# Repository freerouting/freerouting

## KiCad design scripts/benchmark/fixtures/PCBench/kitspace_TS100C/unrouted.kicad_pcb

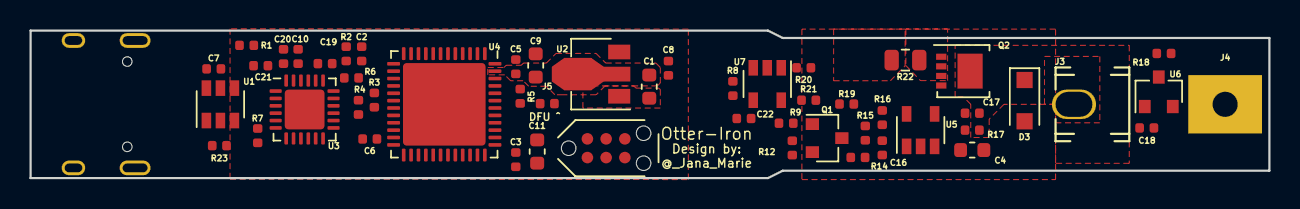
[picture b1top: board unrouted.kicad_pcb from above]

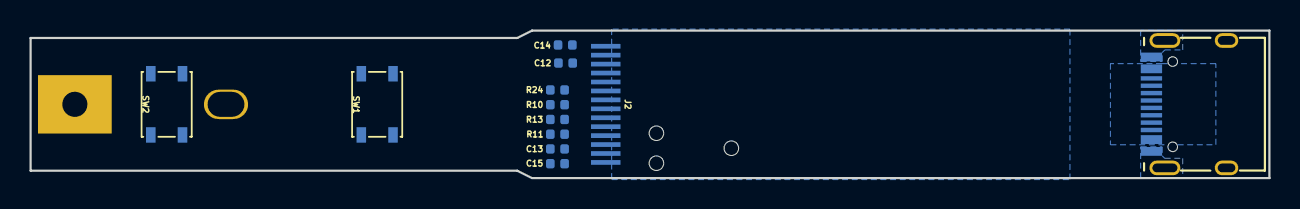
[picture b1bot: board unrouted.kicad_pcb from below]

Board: 2 copper layers, 84.0 x 10.0 mm, 64 parts (12 on the bottom side), 42 nets, no tracks yet.

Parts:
C1, C4, C9, C11: 1μF 25V; C_0603_1608Metric
C2, C3, C5, C6, C7, C8, C10, C18, C21, C22: 0.1μF; C_0402_1005Metric
C12, C13, C14, C15, C19, C20: 1μF 25V; C_0402_1005Metric
C16: 18p; C_0402_1005Metric
C17: DNP; C_0402_1005Metric
D3: B140-E3; D_SOD-123F
J1: USB_C_Receptacle_USB2.0; USB-C 16Pin
J2: OLED_64x32; 0.69OLED
J3: A; Keystone_3621
J4: B; 3622TR
J5: DNP; R_0402_1005Metric
P1: TC2030-CTX; TC2030-NL_SMALL
Q1: SS8050; SOT-23
Q2: DMP3017SFG; Diodes_PowerDI3333-8
R1, R11: 560k; R_0402_1005Metric
R2, R17: 100k; R_0402_1005Metric
R3, R4, R5, R6, R7, R8, R9, R10, R12, R13, R14, R16, R18, R23, R24: 2k37; R_0402_1005Metric
R15: 750k; R_0402_1005Metric
R19: 20; R_0402_1005Metric
R20, R21: 33; R_0402_1005Metric
R22: 10m; R_0805_2012Metric
SW1: key1; SW_SPST_PTS810
SW2: key2; SW_SPST_PTS810
U1: USBLC6-4SC6; SOT-23-6
U2: AP2204R-3.3; SOT-89-3
U3: STUSB4500QTR; QFN-24-1EP_4x4mm_P0.5mm_EP2.7x2.7mm
U4: STM32F072CBUx; QFN-48-1EP_7x7mm_P0.5mm_EP5.6x5.6mm
U5: OPA340NA; SOT-23-5
U6: MCP9700AT-ETT; SOT-23
U7: SI8540; SOT-23-5

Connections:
/OUT: C17.2, D3.1, J3.1, Q2.5, R17.1
CC1: J1.A5, U1.4, U3.1, U3.2
CC2: J1.B5, U1.3, U3.4, U3.5
IIN: C22.1, R8.1, U4.10, U7.4
INT_N: R6.1, U3.19, U4.25
unnamed: C12.1, J2.3
unnamed: C12.2, J2.4
unnamed: C13.1, J2.13
unnamed: C14.1, J2.2
unnamed: C15.1, J2.14
unnamed: C16.1, R15.1, R16.2, U5.4
unnamed: C16.2, R14.1, R15.2, U5.1
unnamed: C19.2, U3.21
unnamed: C20.1, U3.23
unnamed: J2.9, R24.1
unnamed: J2.12, R11.1
unnamed: J5.1, R5.2, U4.44
unnamed: Q1.1, R9.2
unnamed: Q1.3, R12.2, R19.1
unnamed: Q2.1, Q2.2, Q2.3, R21.2, R22.2
unnamed: Q2.4, R19.2
unnamed: R7.2, U3.6
unnamed: R17.2, U5.3
unnamed: R18.2, U6.2
unnamed: R20.2, U7.1
unnamed: R21.1, U7.5
unnamed: R23.1, U3.18
unnamed: SW1.2, U4.13
unnamed: SW2.2, U4.14
OLED_SCL: J2.10, R10.1, U4.42
OLED_SDA: J2.11, R13.1, U4.43
PWM: R9.1, U4.29
SCL: R3.1, U3.7, U4.21
SDA: R4.1, U3.8, U4.22
SWCLK: P1.4, U4.37
SWDIO: P1.2, U4.34
TREF: R18.1, U4.15
TTIP: R14.2, U4.11
UIN: C2.1, R1.2, R2.1, U4.12
USB_N: J1.A7, J1.B7, U1.1, U4.32
USB_P: J1.A6, J1.B6, U1.6, U4.33
nRST: P1.3, U4.7

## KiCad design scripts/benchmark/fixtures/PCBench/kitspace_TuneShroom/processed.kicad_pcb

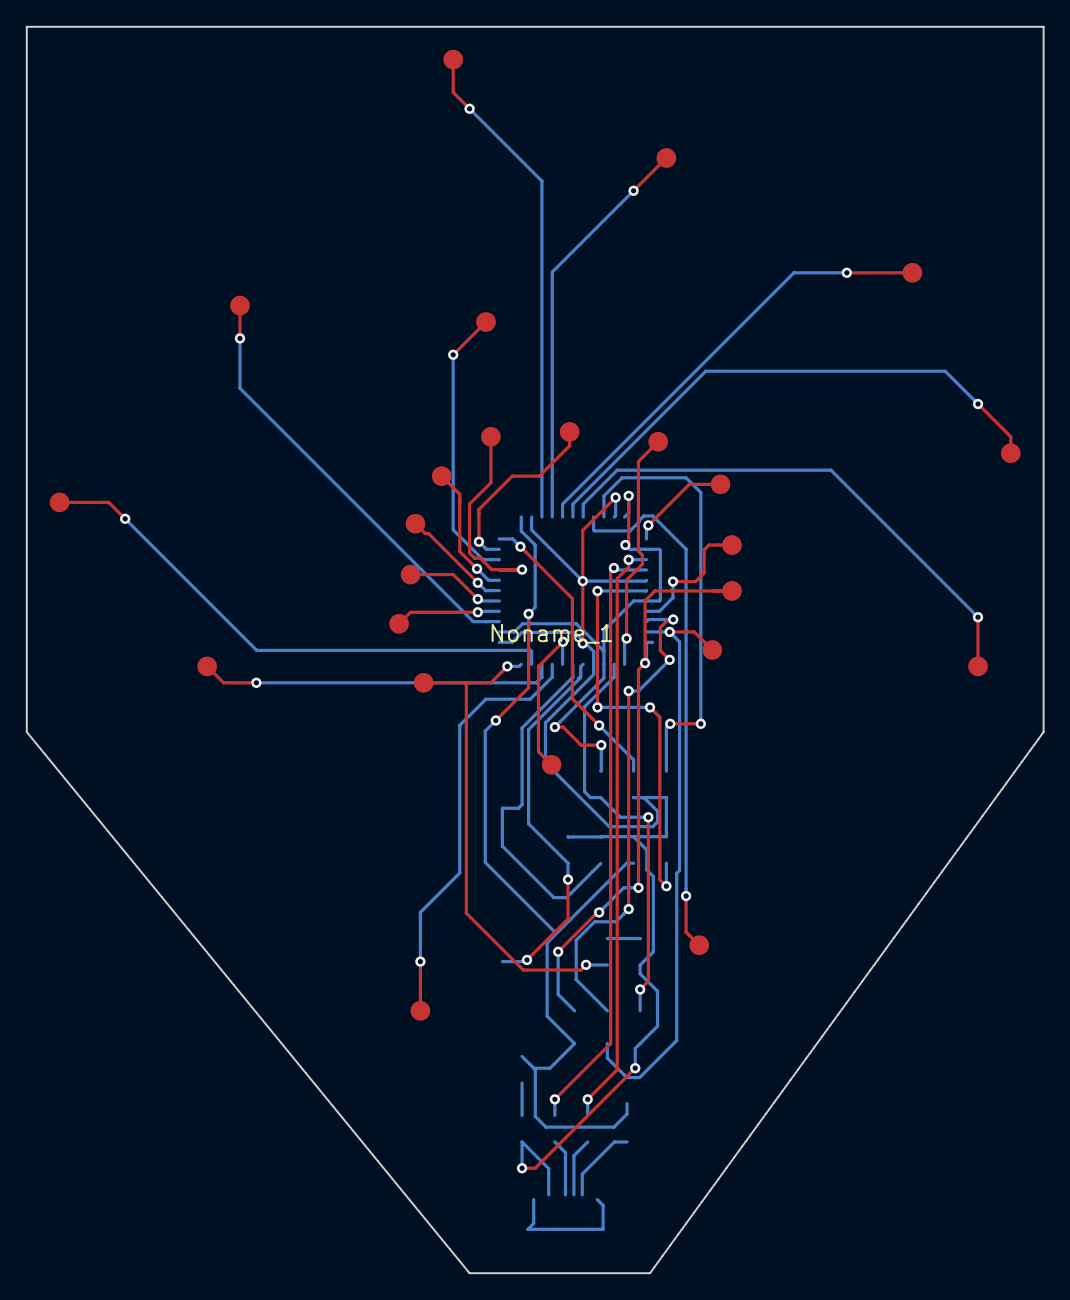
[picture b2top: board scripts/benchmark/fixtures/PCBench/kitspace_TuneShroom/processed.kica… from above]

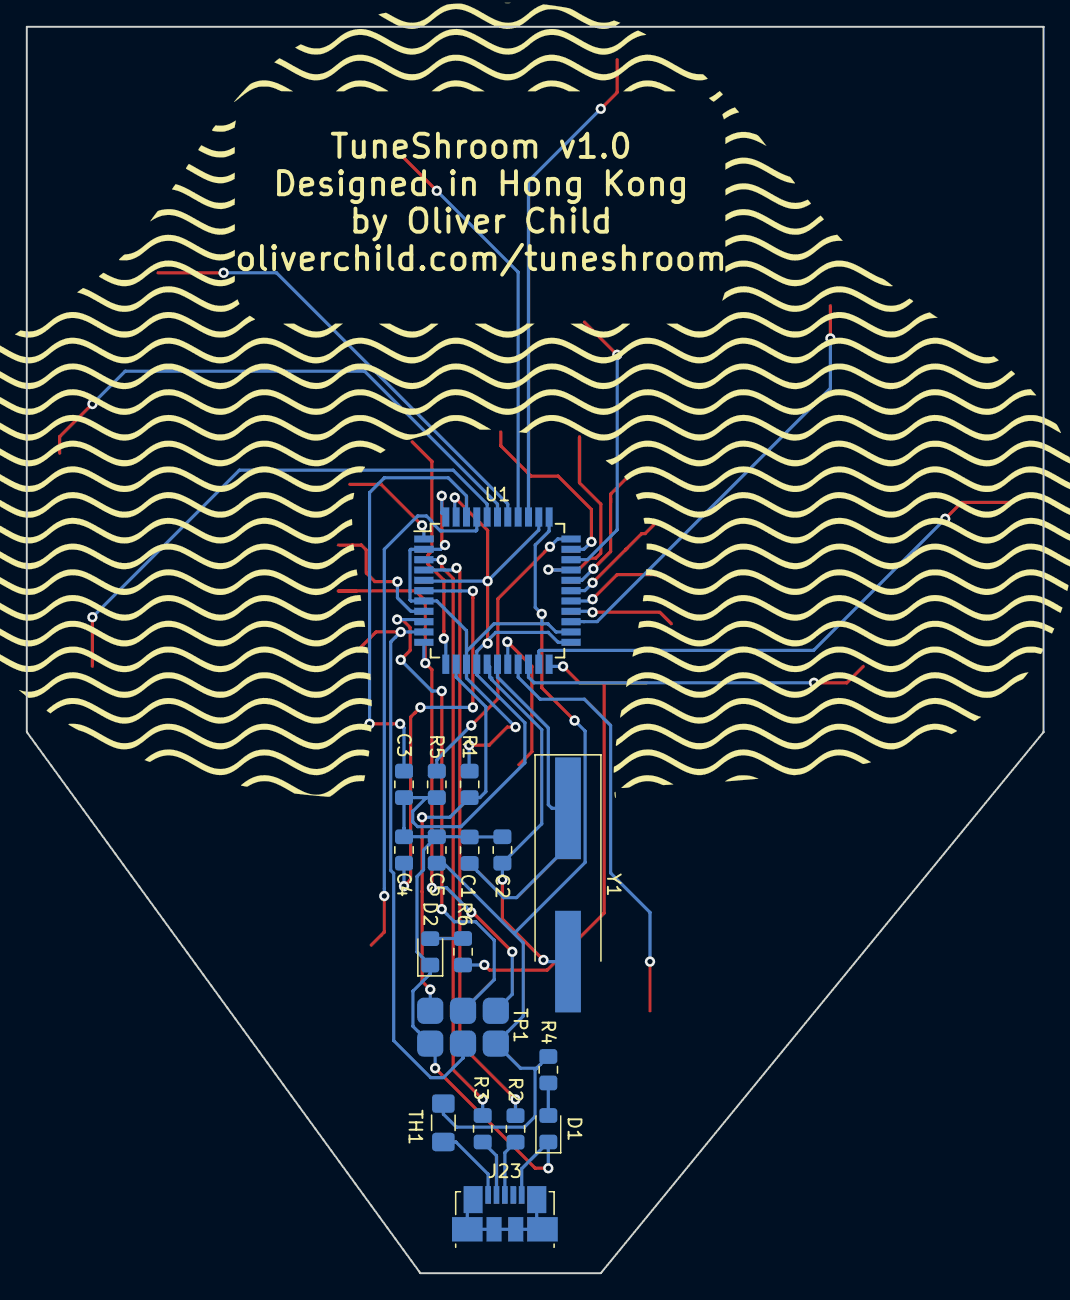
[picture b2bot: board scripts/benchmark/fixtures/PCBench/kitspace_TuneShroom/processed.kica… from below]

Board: 2 copper layers, 78.7 x 96.5 mm, 43 parts (18 on the bottom side), 40 nets.

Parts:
C1, C2: 22pF; C_0805_2012Metric_Pad1.15x1.40mm_HandSolder
C3, C5: 0.1uF; C_0805_2012Metric_Pad1.15x1.40mm_HandSolder
C4: 1uF; C_0805_2012Metric_Pad1.15x1.40mm_HandSolder
D1, D2: LED; LED_0805_2012Metric_Pad1.15x1.40mm_HandSolder
J1, J2, J3, J4, J5, J6, J7, J8, J9, J10, J11, J12, J13, J14, J15, J16, J17, J18, J19, J20, J21, J22, J24, J25: Conn_01x01; contact
J23: USB_B_Micro; USB_Micro-B_Molex_47346-0001
Noname_1: pattern
R1, R5: 10K; R_0805_2012Metric_Pad1.15x1.40mm_HandSolder
R2, R3: 22; R_0805_2012Metric_Pad1.15x1.40mm_HandSolder
R4, R6: 330; R_0805_2012Metric_Pad1.15x1.40mm_HandSolder
TH1: Thermistor; Fuse_1206_3216Metric_Pad1.42x1.75mm_HandSolder
TP1: ICSP
U1: ATmega32U4-AU; TQFP-44_10x10mm_P0.8mm
Y1: 16MHz; Crystal_SMD_HC49-SD_HandSoldering

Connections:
+5V: C5.1, R1.1, R4.1, TH1.1, TP1.2, U1.2, U1.7, U1.14, U1.24, U1.34, U1.44
A0: J1.1, U1.36
A1: J3.1, U1.37
A2: J5.1, U1.38
A3: J7.1, U1.39
A4: J9.1, U1.40
A5: J11.1, U1.41
D0: J13.1, U1.20
D1: J15.1, U1.21
D2: J17.1, U1.19
D3: J19.1, U1.18
D4: J21.1, U1.25
D5: J2.1, U1.31
D6: J4.1, U1.27
D7: J6.1, U1.1
D8: J8.1, U1.28
D9: J10.1, U1.29
D10: J12.1, U1.30
D11: J14.1, U1.12
D12: J16.1, U1.26
D13: J18.1, U1.32
D17: J20.1, U1.8
D+: R2.1, U1.4
D-: R3.1, U1.3
GND: C1.2, C2.2, C3.2, C4.2, C5.2, D1.1, D2.1, J23.5, R5.2, TP1.6, U1.5, U1.15, U1.23, U1.35, U1.43
MISO: J22.1, TP1.1, U1.11
MOSI: J24.1, TP1.4, U1.10
unnamed: C1.1, U1.17, Y1.1
unnamed: C2.1, U1.16, Y1.2
unnamed: C3.1, U1.42
unnamed: C4.1, U1.6
unnamed: D1.2, R4.2
unnamed: D2.2, R6.2
unnamed: J23.1, TH1.2
unnamed: J23.2, R3.2
unnamed: J23.3, R2.2
unnamed: R5.1, U1.33
RESET: R1.2, TP1.5, U1.13
RX_LED: J25.1, R6.1, U1.22
SCK: TP1.3, U1.9

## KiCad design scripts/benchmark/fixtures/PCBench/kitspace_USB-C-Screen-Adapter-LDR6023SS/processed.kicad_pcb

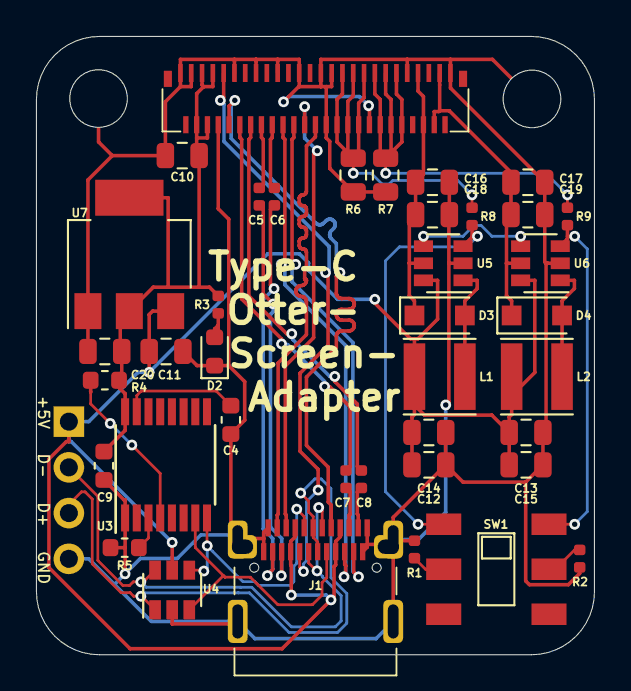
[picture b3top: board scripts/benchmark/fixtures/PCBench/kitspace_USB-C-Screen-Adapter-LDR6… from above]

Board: 2 copper layers, 31.0 x 34.3 mm, 42 parts (0 on the bottom side), 36 nets.

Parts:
C4, C9: 100n; C_0603_1608Metric
C5, C6, C7, C8: 100n; C_0402_1005Metric
C10, C11, C12, C13, C14, C15, C16, C17, C18, C19, C20: 2.2uF; C_0805_2012Metric
D2: LED; LED_0603_1608Metric
D3, D4: SM4007PL; D_SOD-123F
H1, H2: MountingHole_Pad; MountingHole_3.2mm_M3
J1: USB_C_Receptacle; USB_C_24P_SMD
J2: USB; PinHeader_1x04_P2.54mm_Vertical
L1, L2: 22uH; L_Taiyo-Yuden_MD-4040
R1, R2, R3, R8, R9: 1k; R_0402_1005Metric
R4, R5: 10k; R_0603_1608Metric
R6, R7: 1.6; R_0805_2012Metric
SW1: BRIGHTNESS; K3-2235S-K1
U2: 5022505191
U3: LDR6023SS; TSSOP-16_4.4x5mm_P0.65mm
U4: USBLC6-4; SOT-23-6
U5, U6: SY7200AABC; SOT-23-6
U7: AMS1117-3.3; SOT-223-3_TabPin2

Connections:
+3V3: C9.1, C10.1, C20.1, R3.2, R4.2, U2.4, U2.5, U2.6, U2.7, U3.16, U7.2
+5V: C11.1, C12.1, C13.1, C14.1, C15.1, J1.A4, J1.A9, J1.B4, J1.B9, J2.1, L1.1, L2.1, U4.5, U5.6, U6.6, U7.3
/_L0_N: C7.2, J1.A10
/_L0_P: C8.2, J1.A11
/_L1_N: C5.2, J1.B10
/_L1_P: C6.2, J1.B11
AUX_N: J1.A8, U2.10
AUX_P: J1.B8, U2.9
CC1: J1.A5, U3.8, U4.4
CC2: J1.B5, U3.7, U4.3
GND: C4.2, C9.2, C10.2, C11.2, C12.2, C13.2, C14.2, C15.2, C16.2, C17.2, C18.2, C19.2, C20.2, D2.1, H1.1, H2.1, J1.A1, J1.A12, J1.B1, J1.B12, J1.S1, J2.4, R1.1, R2.1, R5.2, R6.2, R7.2, U2.1, U2.3, U2.8, U2.11, U2.15, U2.19, U2.23, U2.27, U2.28, U2.29, U2.36, U2.43, U2.51, U3.1, U4.2, U5.2, U6.2, U7.1
L0_N: C7.1, U2.12
L0_P: C8.1, U2.14
L1_N: C5.1, U2.16
L1_P: C6.1, U2.18
L2_N: J1.B3, U2.20
L2_P: J1.B2, U2.22
L3_N: J1.A3, U2.24
L3_P: J1.A2, U2.26
LEDA1: C17.1, C19.1, D4.1, U2.48, U2.49, U6.5
LEDA2: C16.1, C18.1, D3.1, U2.45, U2.46, U5.5
LEDC1: R7.1, R9.2, U2.37, U2.38, U2.39, U2.40, U2.41, U2.42
LEDC1DIM: R9.1, SW1.4, U6.3
LEDC2: R6.1, R8.2, U2.30, U2.31, U2.32, U2.33, U2.34, U2.35
LEDC2DIM: R8.1, SW1.1, U5.3
unnamed: C4.1, U3.15
unnamed: D2.2, R3.1
unnamed: D3.2, L1.2, U5.1
unnamed: D4.2, L2.2, U6.1
unnamed: R1.2, SW1.2
unnamed: R2.2, SW1.5
unnamed: R4.1, U3.4
unnamed: R5.1, U3.3
PWM: U5.4, U6.4
USB_N: J1.A7, J1.B7, J2.2, U4.6
USB_P: J1.A6, J1.B6, J2.3, U4.1

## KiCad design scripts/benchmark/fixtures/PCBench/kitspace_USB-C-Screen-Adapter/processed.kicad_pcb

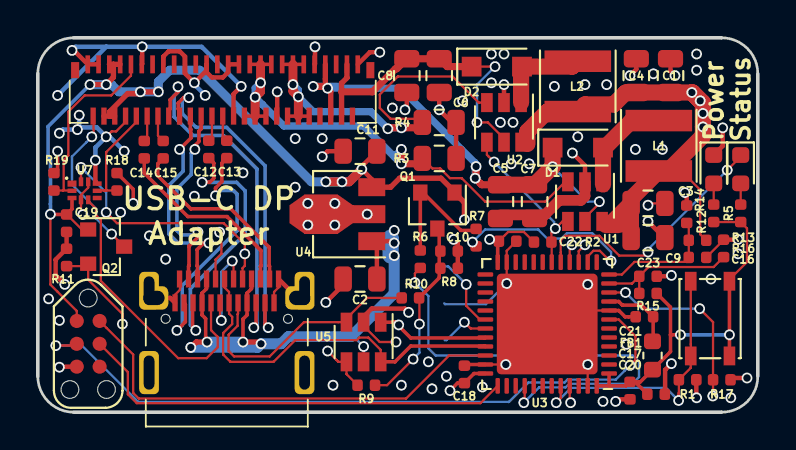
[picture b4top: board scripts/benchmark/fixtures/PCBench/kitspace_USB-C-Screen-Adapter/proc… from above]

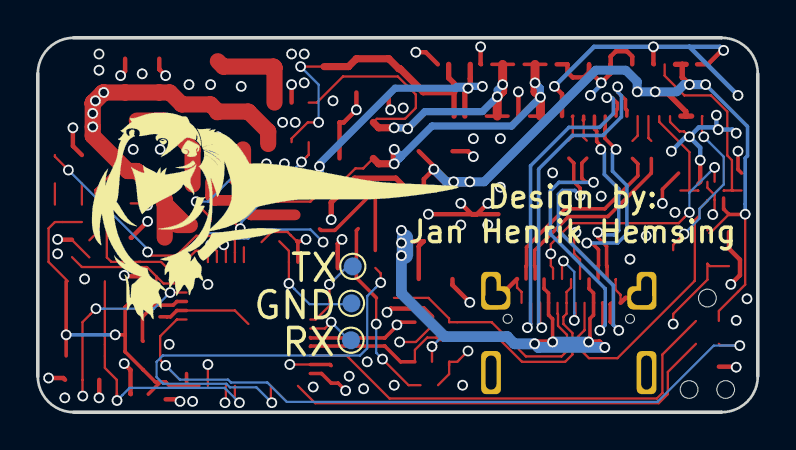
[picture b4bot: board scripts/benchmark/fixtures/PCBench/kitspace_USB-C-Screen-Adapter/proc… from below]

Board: 4 copper layers, 40.0 x 20.8 mm, 64 parts (3 on the bottom side), 51 nets.

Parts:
C1, C2, C3, C4, C5, C6, C7, C8, C9, C11: 2.2uF; C_0805_2012Metric
C10: 820p; C_0402_1005Metric
C12, C13, C14, C15, C16, C17, C18, C19, C20, C21, C22: 100n; C_0402_1005Metric
C23: 220n; C_0402_1005Metric
D1, D2: SM4007PL; D_SOD-123F
D3, D4: LED; LED_0603_1608Metric
FB1: FERRET; L_0603_1608Metric
J1: USB_C_Receptacle; USB_C_24P_SMD
L1, L2: 22uH; L_Taiyo-Yuden_MD-4040
P1: TC2030-CTX-Tag-Connect; TC2030
Q1, Q2: 2N7002; SOT-23
R1, R2, R8: 5k1; R_0402_1005Metric
R3, R4: 0.8; R_0805_2012Metric
R5, R12: 1k; R_0402_1005Metric
R6: 169; R_0402_1005Metric
R7: 75; R_0402_1005Metric
R9, R10, R18, R19: 0; R_0402_1005Metric
R11: 1M; R_0402_1005Metric
R13: 8k2; R_0402_1005Metric
R14: 1k5; R_0402_1005Metric
R15, R17: 24k; R_0402_1005Metric
R16: 4k7; R_0402_1005Metric
SW1: DFU; SW_SPST_PTS810
TP1: UART_TX; TestPoint_Pad_D1.0mm
TP2: UART_RX; TestPoint_Pad_D1.0mm
TP3: GND; TestPoint_Pad_D1.0mm
U1, U2: SY7200AABC; SOT-23-6
U3: STM32F072CBUx; QFN-48-1EP_7x7mm_P0.5mm_EP5.6x5.6mm
U4: AP2204R-3.3; SOT-89-3
U5: USBLC6-4; SOT-23-6
U6: 5022505191
U7: STG3684A; QFN10L

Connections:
+3V3: C11.1, C17.1, C18.1, C19.1, C20.1, C22.1, FB1.2, P1.1, Q1.1, Q2.1, R2.1, R5.2, R12.2, R15.2, SW1.2, U3.1, U3.24, U3.36, U3.48, U4.3, U6.4, U6.5, U6.6, U6.7, U7.3
+5V: C1.1, C2.1, C3.1, C4.1, C9.1, J1.A4, J1.A9, J1.B4, J1.B9, L1.1, L2.1, R13.2, U1.6, U2.6, U4.1, U5.5
/_L0_N: C14.2, J1.A10
/_L0_P: C15.2, J1.A11
/_L3_N: C12.2, J1.B10
/_L3_P: C13.2, J1.B11
AUX_N: R18.1, U6.10, U7.7
AUX_P: R19.1, U6.9, U7.2
CC1: J1.A5, R9.1, U5.4
CC2: J1.B5, R10.1, U5.3
CC_RX: R7.2, U3.14
CC_TX: R6.2, U3.40
DFU: R1.2, SW1.1, U3.44
GND: C1.2, C2.2, C3.2, C4.2, C5.2, C6.2, C7.2, C8.2, C9.2, C10.2, C11.2, C16.2, C17.2, C18.2, C19.2, C20.2, C21.2, C22.2, C23.2, D4.1, J1.A1, J1.A12, J1.B1, J1.B12, J1.S1, P1.5, R1.1, R3.2, R4.2, R8.2, R11.1, R14.1, R16.1, R17.1, TP3.1, U1.2, U2.2, U3.8, U3.23, U3.35, U3.47, U3.49, U4.2, U5.2, U6.1, U6.3, U6.8, U6.11, U6.15, U6.19, U6.23, U6.27, U6.28, U6.29, U6.36, U6.43, U6.51, U7.8
HPD: Q2.3, U6.2
L0_N: C14.1, U6.12
L0_P: C15.1, U6.14
L1_N: J1.B3, U6.16
L1_P: J1.B2, U6.18
L2_N: J1.A3, U6.20
L2_P: J1.A2, U6.22
L3_N: C12.1, U6.24
L3_P: C13.1, U6.26
LEDA1: C6.1, C8.1, D2.1, U2.5, U6.48, U6.49
LEDA2: C5.1, C7.1, D1.1, U1.5, U6.45, U6.46
LEDC1: R4.1, U2.3, U6.37, U6.38, U6.39, U6.40, U6.41, U6.42
LEDC2: R3.1, U1.3, U6.30, U6.31, U6.32, U6.33, U6.34, U6.35
NRST: P1.3, U3.7
unnamed: C10.1, Q1.3, R8.1, R9.2, R10.2
unnamed: D1.2, L1.2, U1.1
unnamed: D2.2, L2.2, U2.1
unnamed: D3.1, U3.17
unnamed: D3.2, R5.1
unnamed: D4.2, R12.1
unnamed: Q1.2, R6.1, R7.1
unnamed: TP1.1, U3.30
unnamed: TP2.1, U3.31
PWM: R2.2, U1.4, U2.4, U3.18
RXREF: C23.1, R15.1, R16.2, U3.11
SBU1: J1.A8, U7.10
SBU2: J1.B8, U7.5
SBU_ENABLE: R17.2, U3.10, U7.4, U7.9
STM_HPD: Q2.2, R11.2, U3.45
SWCLK: P1.4, U3.37
SWDIO: P1.2, U3.34
USB_N: J1.A7, J1.B7, U3.32, U5.1
USB_P: J1.A6, J1.B6, U3.33, U5.6
VBUS_SENSE: C16.1, R13.1, R14.2, U3.12
VDDA: C21.1, FB1.1, U3.9
_DP_AUX_N: R18.2, U3.15
_DP_AUX_P: R19.2, U3.16
